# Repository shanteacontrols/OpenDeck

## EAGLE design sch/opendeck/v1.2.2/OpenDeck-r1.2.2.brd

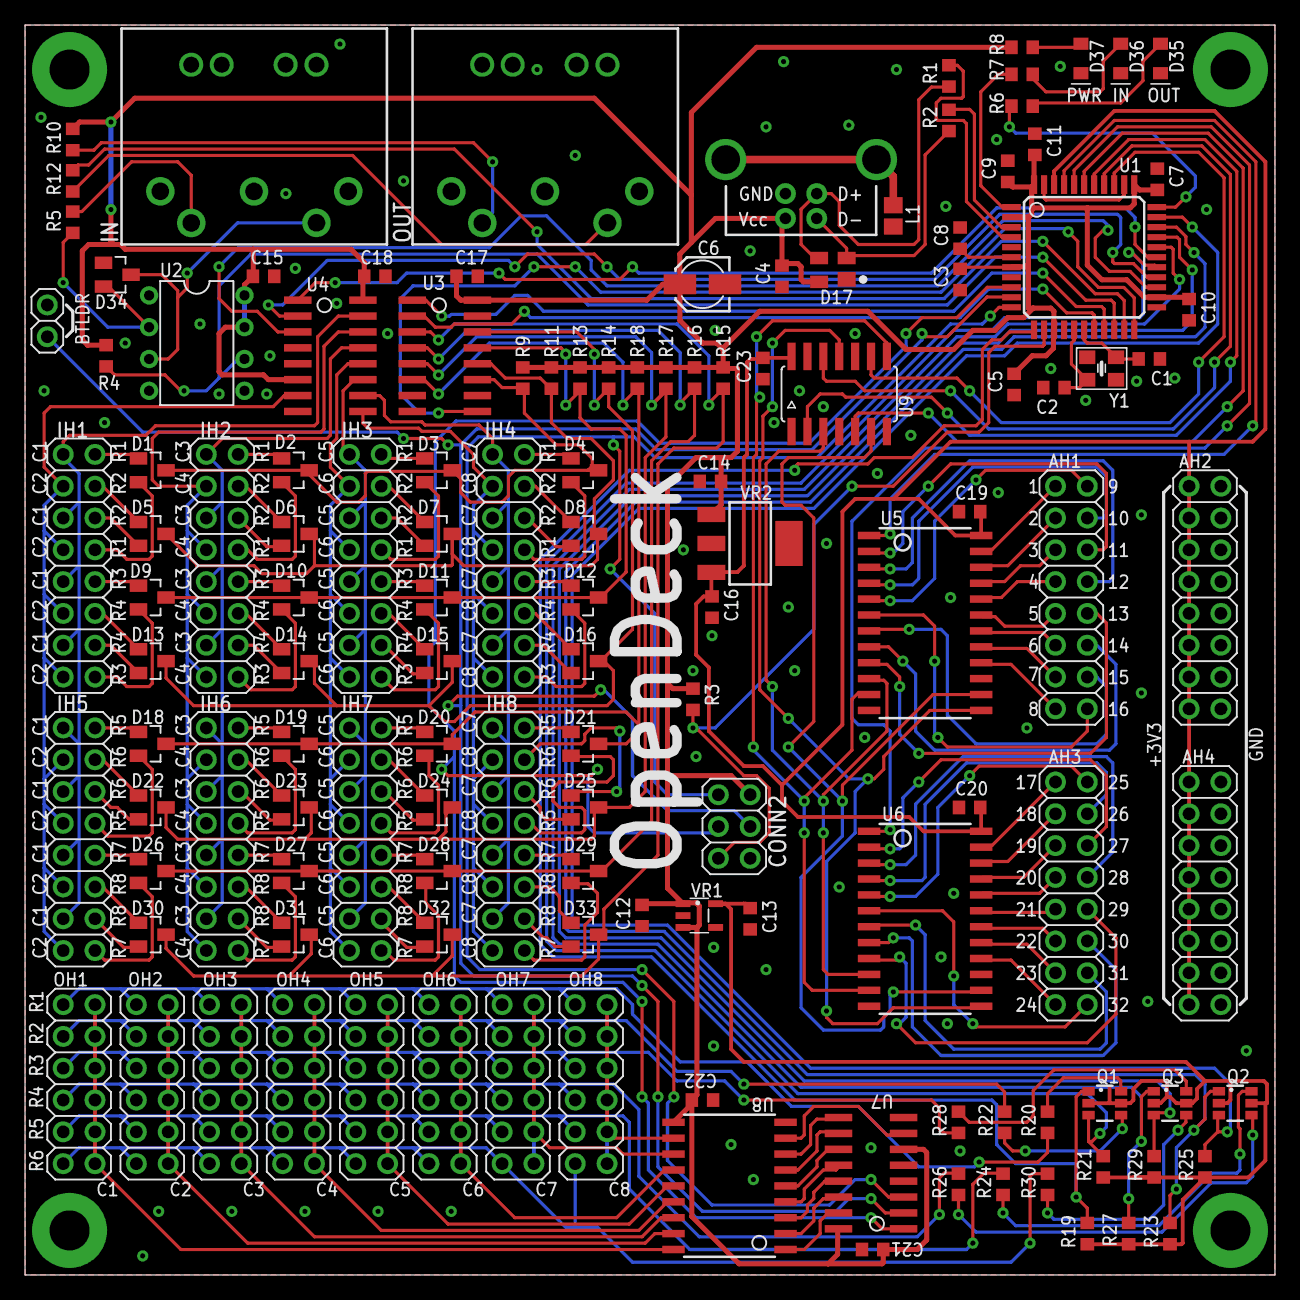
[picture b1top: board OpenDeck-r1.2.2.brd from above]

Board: 2 copper layers, 99.8 x 99.8 mm, 131 parts (0 on the bottom side), 190 nets.

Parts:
AH1, AH2, AH3, AH4: PINHD-2X08-TH-2.54MM; 2X08-2.54
C1, C2: 22p; C0603
C3, C4, C5, C7, C9, C10, C11, C15, C17, C18, C19, C20, C21, C22, C23: 100n; C0603
C6: 10u; 153CLV-0405
C8: 1u; C0603
C12, C13, C14, C16: 4.7u; C0603
CONN1: USB-B-PTH
CONN2: PINHD-2X03-TH-2.54MM-V; 2X03-2.54-V
CONN3, CONN4: MIDI_CONN-STD; DIN5_SUPPORT
CONN5: PINHD-1X02-TH-2.54MM; 1X02-2.54-V
D1, D2, D3, D4, D5, D6, D7, D8, D9, D10, D11, D12, D13, D14, D15, D16, D18, D19, D20, D21, D22, D23, D24, D25, D26, D27, D28, D29, D30, D31, D32, D33, D34: BAW56; SOT23
D17: PRTR5V0U2X; SOT143
D35: Red; 0805_LED
D36: Yellow; 0805_LED
D37: Green; 0805_LED
IH1, IH2, IH3, IH4, IH5, IH6, IH7, IH8: PINHD-2X08-TH-2.54MM; 2X08-2.54
L1: FERRITE_BEAD-BLM21PG221SN1D; L0805
OH1, OH2, OH3, OH4, OH5, OH6, OH7, OH8: PINHD-2X06-TH-2.54MM; 2X06-2.54-V
Q1, Q2, Q3: FDC6312P; SSOT6
R1, R2: 22; R0603
R3, R4, R9, R11, R13, R14, R15, R16, R17, R18: 10k; R0603
R5, R10, R12: 220; R0603
R6, R7, R8: 1k; R0603
R19, R21, R23, R25, R27, R29: 4k7; R0603
R20, R22, R24, R26, R28, R30: 47; R0603
U1: ATMEGA-32U4TQFP; TQFP-44
U2: 6N137; DIL08
U3: 74HC165; SO16
U4: 74HC138-SO; SO16
U5, U6: MC14067BDWR2G-SO24W; SO24-W
U7: 74HC238-SO; SO16
U8: ULN2803A-SO; SO18
U9: 74AHC125; SOIC14
VR1: LP5907-4.5V; SOT23-5
VR2: MCP1825; SOT223
Y1: 16MHz; CRYSTAL-SMD-3.2X2.5

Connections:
+5V: C3.1, C4.2, C5.1, C6.+, C7.1, C9.1, C10.1, C11.1, C12.1, C14.1, C15.2, C17.2, C18.2, C21.1, C22.1, CONN1.VBUS, CONN2.2, D17.4, R3.1, R4.1, R8.1, R9.1, R10.2, R11.1, R13.1, R14.1, R15.1, R16.1, R17.1, R18.1, U1.2, U1.7, U1.14, U1.24, U1.34, U1.44, U2.7, U2.8, U3.16, U4.6, U4.16, U7.6, U7.16, U8.10, VR1.1, VR1.3, VR2.1
AREF: AH2.1, AH2.3, AH2.5, AH2.7, AH2.9, AH2.11, AH2.13, AH2.15, AH4.1, AH4.3, AH4.5, AH4.7, AH4.9, AH4.11, AH4.13, AH4.15, C16.1, C19.2, C20.2, C23.2, U1.42, U5.24, U6.24, U9.14, VR2.3
A_IN_1: AH1.1, U5.23
A_IN_2: AH1.3, U5.22
A_IN_3: AH1.5, U5.21
A_IN_4: AH1.7, U5.20
A_IN_5: AH1.9, U5.19
A_IN_6: AH1.11, U5.18
A_IN_7: AH1.13, U5.17
A_IN_8: AH1.15, U5.16
A_IN_9: AH1.6, U5.2
A_IN_10: AH1.8, U5.3
A_IN_11: AH1.4, U5.4
A_IN_12: AH1.2, U5.5
A_IN_13: AH1.16, U5.6
A_IN_14: AH1.14, U5.7
A_IN_15: AH1.12, U5.8
A_IN_16: AH1.10, U5.9
A_IN_17: AH3.1, U6.23
A_IN_18: AH3.3, U6.22
A_IN_19: AH3.5, U6.21
A_IN_20: AH3.7, U6.20
A_IN_21: AH3.9, U6.19
A_IN_22: AH3.11, U6.18
A_IN_23: AH3.13, U6.17
A_IN_24: AH3.15, U6.16
A_IN_25: AH3.6, U6.2
A_IN_26: AH3.8, U6.3
A_IN_27: AH3.4, U6.4
A_IN_28: AH3.2, U6.5
A_IN_29: AH3.16, U6.6
A_IN_30: AH3.14, U6.7
A_IN_31: AH3.12, U6.8
A_IN_32: AH3.10, U6.9
BC_1: IH1.1, IH1.5, IH1.9, IH1.13, IH5.1, IH5.5, IH5.9, IH5.13, U4.15
BC_2: IH1.3, IH1.7, IH1.11, IH1.15, IH5.3, IH5.7, IH5.11, IH5.15, U4.7
BC_3: IH2.1, IH2.5, IH2.9, IH2.13, IH6.1, IH6.5, IH6.9, IH6.13, U4.13
BC_4: IH2.3, IH2.7, IH2.11, IH2.15, IH6.3, IH6.7, IH6.11, IH6.15, U4.14
BC_5: IH3.1, IH3.5, IH3.9, IH3.13, IH7.1, IH7.5, IH7.9, IH7.13, U4.11
BC_6: IH3.3, IH3.7, IH3.11, IH3.15, IH7.3, IH7.7, IH7.11, IH7.15, U4.12
BC_7: IH4.1, IH4.5, IH4.9, IH4.13, IH8.1, IH8.5, IH8.9, IH8.13, U4.10
BC_8: IH4.3, IH4.7, IH4.11, IH4.15, IH8.3, IH8.7, IH8.11, IH8.15, U4.9
BR_1: D1.3, D2.3, D3.3, D4.3, R9.2, U3.11
BR_2: D5.3, D6.3, D7.3, D8.3, R11.2, U3.12
BR_3: D9.3, D10.3, D11.3, D12.3, R13.2, U3.13
BR_4: D13.3, D14.3, D15.3, D16.3, R14.2, U3.14
BR_5: D30.3, D31.3, D32.3, D33.3, R15.2, U3.3
BR_6: D26.3, D27.3, D28.3, D29.3, R16.2, U3.4
BR_7: D22.3, D23.3, D24.3, D25.3, R17.2, U3.5
BR_8: D18.3, D19.3, D20.3, D21.3, R18.2, U3.6
D+: R1.2, U1.4
D+X: CONN1.D+, D17.3, R1.1
D-: R2.1, U1.3
D-X: CONN1.D-, D17.2, R2.2
DEC_BM_A0: U1.28, U4.1
DEC_BM_A1: U1.26, U4.2
DEC_BM_A2: U1.25, U4.3
DEC_LM_A0/SCK: CONN2.3, U1.9, U7.1
DEC_LM_A1/MOSI: CONN2.4, CONN5.1, U1.10, U7.2
DEC_LM_A2/MISO: CONN2.1, U1.11, U7.3
DEC_LM_Y0: U7.15, U8.1
DEC_LM_Y1: U7.14, U8.2
DEC_LM_Y2: U7.13, U8.3
DEC_LM_Y3: U7.12, U8.4
DEC_LM_Y4: U7.11, U8.5
DEC_LM_Y5: U7.10, U8.6
DEC_LM_Y6: U7.9, U8.7
DEC_LM_Y7: U7.7, U8.8
GND: AH2.2, AH2.4, AH2.6, AH2.8, AH2.10, AH2.12, AH2.14, AH2.16, AH4.2, AH4.4, AH4.6, AH4.8, AH4.10, AH4.12, AH4.14, AH4.16, C1.2, C2.2, C3.2, C4.1, C5.2, C6.-, C7.2, C8.2, C9.2, C10.2, C11.2, C12.2, C13.2, C14.2, C15.1, C16.2, C17.1, C18.1, C19.1, C20.1, C21.2, C22.2, C23.1, CONN1.GND, CONN2.6, CONN4.2, CONN5.2, D17.1, D35.C, D36.C, D37.C, L1.1, U1.5, U1.15, U1.23, U1.35, U1.43, U2.5, U3.8, U3.15, U4.4, U4.5, U4.8, U5.12, U5.15, U6.12, U6.15, U7.4, U7.5, U7.8, U8.9, U9.1, U9.4, U9.7, U9.10, U9.13, VR1.2, VR2.2, VR2.4
IH1_2: D1.1, IH1.2
IH1_4: D5.1, IH1.4
IH1_6: D5.2, IH1.6
IH1_8: D1.2, IH1.8
IH1_10: D9.1, IH1.10
IH1_12: D13.1, IH1.12
IH1_14: D13.2, IH1.14
IH1_16: D9.2, IH1.16
IH2_2: D2.1, IH2.2
IH2_4: D6.1, IH2.4
IH2_6: D6.2, IH2.6
IH2_8: D2.2, IH2.8
IH2_10: D10.1, IH2.10
IH2_12: D14.1, IH2.12
IH2_14: D14.2, IH2.14
IH2_16: D10.2, IH2.16
IH3_2: D3.1, IH3.2
IH3_4: D7.1, IH3.4
IH3_6: D7.2, IH3.6
IH3_8: D3.2, IH3.8
IH3_10: D11.1, IH3.10
IH3_12: D15.1, IH3.12
IH3_14: D15.2, IH3.14
IH3_16: D11.2, IH3.16
IH4_2: D4.1, IH4.2
IH4_4: D8.1, IH4.4
IH4_6: D8.2, IH4.6
IH4_8: D4.2, IH4.8
IH4_10: D12.1, IH4.10
IH4_12: D16.1, IH4.12
IH4_14: D16.2, IH4.14
IH4_16: D12.2, IH4.16
IH5_2: D18.1, IH5.2
IH5_4: D22.1, IH5.4
IH5_6: D22.2, IH5.6
IH5_8: D18.2, IH5.8
IH5_10: D26.1, IH5.10
IH5_12: D30.1, IH5.12
IH5_14: D30.2, IH5.14
IH5_16: D26.2, IH5.16
IH6_2: D19.1, IH6.2
IH6_4: D23.1, IH6.4
IH6_6: D23.2, IH6.6
IH6_8: D19.2, IH6.8
IH6_10: D27.1, IH6.10
IH6_12: D31.1, IH6.12
IH6_14: D31.2, IH6.14
IH6_16: D27.2, IH6.16
IH7_2: D20.1, IH7.2
IH7_4: D24.1, IH7.4
IH7_6: D24.2, IH7.6
IH7_8: D20.2, IH7.8
IH7_10: D28.1, IH7.10
IH7_12: D32.1, IH7.12
IH7_14: D32.2, IH7.14
IH7_16: D28.2, IH7.16
IH8_2: D21.1, IH8.2
IH8_4: D25.1, IH8.4
IH8_6: D25.2, IH8.6
IH8_8: D21.2, IH8.8
IH8_10: D29.1, IH8.10
IH8_12: D33.1, IH8.12
IH8_14: D33.2, IH8.14
IH8_16: D29.2, IH8.16
LC_1: OH1.2, OH1.4, OH1.6, OH1.8, OH1.10, OH1.12, U8.18
LC_2: OH2.2, OH2.4, OH2.6, OH2.8, OH2.10, OH2.12, U8.17
LC_3: OH3.2, OH3.4, OH3.6, OH3.8, OH3.10, OH3.12, U8.16
LC_4: OH4.2, OH4.4, OH4.6, OH4.8, OH4.10, OH4.12, U8.15
LC_5: OH5.2, OH5.4, OH5.6, OH5.8, OH5.10, OH5.12, U8.14
LC_6: OH6.2, OH6.4, OH6.6, OH6.8, OH6.10, OH6.12, U8.13
LC_7: OH7.2, OH7.4, OH7.6, OH7.8, OH7.10, OH7.12, U8.12
LC_8: OH8.2, OH8.4, OH8.6, OH8.8, OH8.10, OH8.12, U8.11
LEDS_VCC: C13.1, Q1.2, Q1.5, Q2.2, Q2.5, Q3.2, Q3.5, R19.1, R21.1, R23.1, R25.1, R27.1, R29.1, VR1.5
LR_1_MI: Q1.1, R19.2, U1.12
LR_1_MO: OH1.1, OH2.1, OH3.1, OH4.1, OH5.1, OH6.1, OH7.1, OH8.1, R20.1
LR_1_MO_R: Q1.6, R20.2
LR_2_MI: Q1.3, R21.2, U1.27
LR_2_MO: OH1.3, OH2.3, OH3.3, OH4.3, OH5.3, OH6.3, OH7.3, OH8.3, R22.2
LR_2_MO_R: Q1.4, R22.1
LR_3_MI: Q3.1, R27.2, U1.29
LR_3_MO: OH1.5, OH2.5, OH3.5, OH4.5, OH5.5, OH6.5, OH7.5, OH8.5, R28.1
LR_3_MO_R: Q3.6, R28.2
LR_4_MI: Q2.3, R25.2, U1.32
LR_4_MO: OH1.7, OH2.7, OH3.7, OH4.7, OH5.7, OH6.7, OH7.7, OH8.7, R26.1
LR_4_MO_R: Q2.4, R26.2
LR_5_MI: Q2.1, R23.2, U1.31
LR_5_MO: OH1.9, OH2.9, OH3.9, OH4.9, OH5.9, OH6.9, OH7.9, OH8.9, R24.1
LR_5_MO_R: Q2.6, R24.2
LR_6_MI: Q3.3, R29.2, U1.30
LR_6_MO: OH1.11, OH2.11, OH3.11, OH4.11, OH5.11, OH6.11, OH7.11, OH8.11, R30.1
LR_6_MO_R: Q3.4, R30.2
MIDI_IN: R4.2, U1.20, U2.6
MIDI_IN_4: CONN3.4, R5.1
MIDI_IN_5: CONN3.5, D34.3, U2.3
MIDI_IN_DIODE_OUT: D34.2, R5.2, U2.2
MIDI_IN_LED: R7.2, U1.1
MIDI_IN_LED_R: D36.A, R7.1
MIDI_OUT: R12.2, U1.21
MIDI_OUT_4: CONN4.4, R10.1
MIDI_OUT_5: CONN4.5, R12.1
MIDI_OUT_LED: R6.2, U1.33
MIDI_OUT_LED_R: D35.A, R6.1
MUX_COMMON_1: U1.41, U5.1
MUX_COMMON_2: U1.40, U6.1
MUX_S0_3V3: U5.10, U6.10, U9.3
MUX_S0_5V: U1.38, U9.2
MUX_S1_3V3: U5.11, U6.11, U9.8
MUX_S1_5V: U1.36, U9.9
MUX_S2_3V3: U5.14, U6.14, U9.6
MUX_S2_5V: U1.39, U9.5
MUX_S3_3V3: U5.13, U6.13, U9.11
MUX_S3_5V: U1.37, U9.12
PWR_LED_R: D37.A, R8.2
RESET: CONN2.5, R3.2, U1.13
SR_CLOCK: U1.18, U3.2
SR_OUT: U1.22, U3.9
SR_PARALLEL_LOAD: U1.19, U3.1
UCAP: C8.1, U1.6
USB_SHIELD: CONN1.S1, CONN1.S2, L1.2
XTAL1: C1.1, U1.17, Y1.3
XTAL2: C2.1, U1.16, Y1.1

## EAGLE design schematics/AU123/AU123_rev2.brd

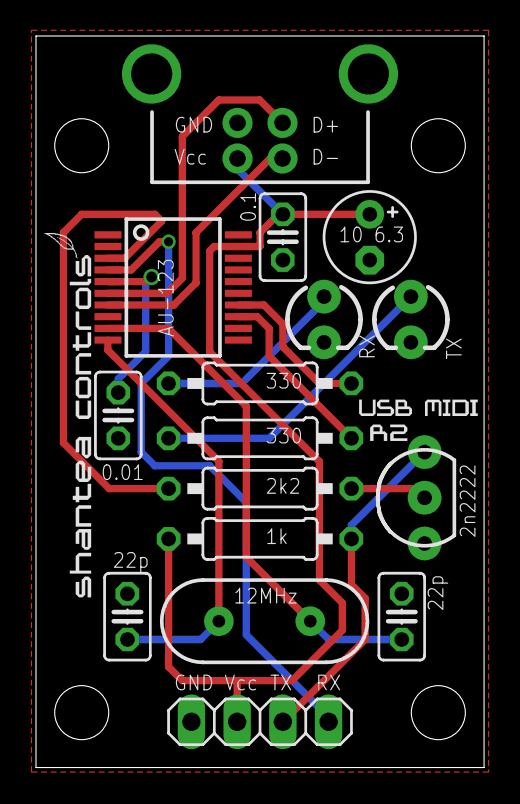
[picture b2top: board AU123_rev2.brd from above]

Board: 2 copper layers, 24.9 x 40.6 mm, 16 parts (0 on the bottom side), 15 nets.

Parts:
E$1: 1X04
E$2, E$3, E$4, E$10: C025-025X050
E$5, E$6, E$7, E$14: 0207/10
E$8, E$9: LED3MM
E$11: USB-B-PTH
E$13: E2,5-5
E$16: TO-92-AMMO
E$26: SSOP20
E$56: HC49US

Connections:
D+: E$11.D+, E$26.6
D-: E$11.D-, E$26.7
GND: E$1.1, E$2.1, E$3.2, E$4.2, E$8.K, E$9.K, E$10.2, E$11.GND, E$11.S1, E$11.S2, E$13.-, E$16.1, E$26.1, E$26.8, E$26.17
MIDI_OUT: E$5.2, E$26.3
MID_IN: E$1.4, E$26.4
RX_LED: E$6.1, E$9.A
S$4: E$6.2, E$26.14
S$7: E$5.1, E$16.2
S$8: E$1.3, E$14.1, E$16.3
TX: E$7.2, E$26.13
TX_LED: E$7.1, E$8.A
V3: E$10.1, E$26.5
VCC: E$1.2, E$2.2, E$11.VBUS, E$13.+, E$14.2, E$26.19
XI: E$4.1, E$26.9, E$56.2
XO: E$3.1, E$26.10, E$56.1

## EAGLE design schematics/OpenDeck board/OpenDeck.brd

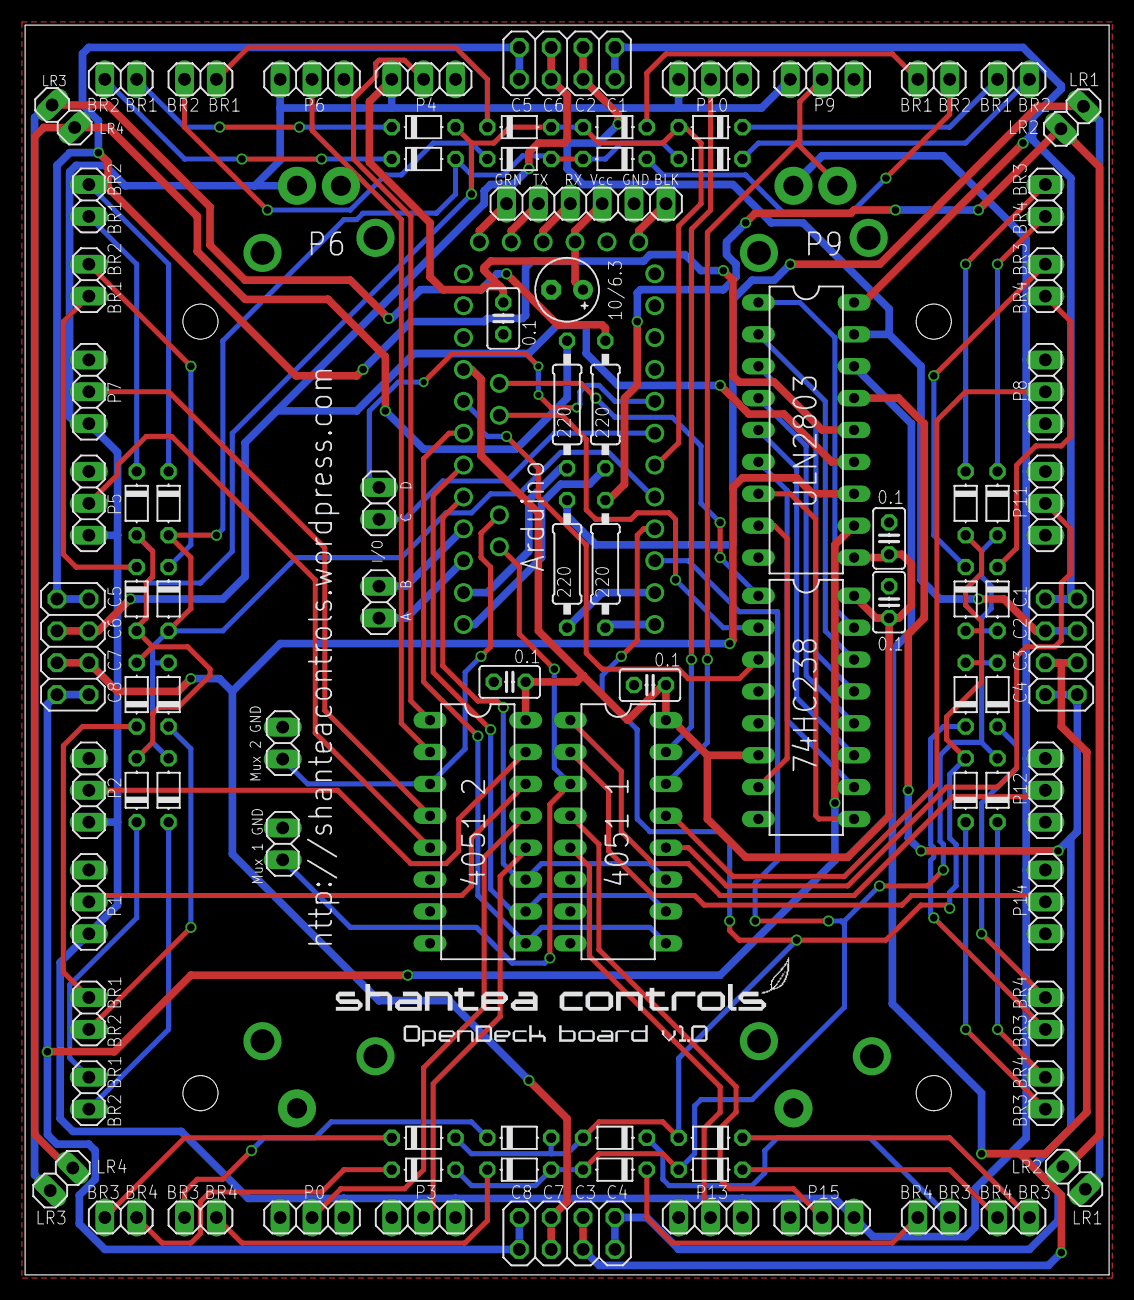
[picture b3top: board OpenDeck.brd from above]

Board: 2 copper layers, 86.4 x 99.6 mm, 92 parts (1 on the bottom side), 95 nets.

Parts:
E$1: ARDUINO_PRO_MINI
E$2, E$3, E$7, E$11, E$14, E$18, E$22, E$35, E$41, E$42, E$43, E$46, E$47, E$62, E$64, E$73, E$74, E$82, E$87, E$88, E$94, E$95, E$96, E$97: 1X02
E$4, E$32, E$33, E$81: 0207/10
E$5: E2,5-5
E$6, E$9, E$20, E$63: 2X04
E$8, E$48, E$51, E$52, E$53, E$54, E$59, E$60, E$61, E$75, E$76, E$77, E$78, E$98, E$100, E$101: 1X03
E$10, E$12, E$16, E$17, E$19, E$21, E$23, E$24, E$25, E$26, E$27, E$28, E$29, E$30, E$31, E$34, E$36, E$37, E$38, E$39, E$40, E$44, E$45, E$65, E$66, E$67, E$68, E$69, E$70, E$71, E$72, E$92: D-5
E$13, E$49, E$84: DIL16
E$15, E$50, E$85, E$86, E$89: C025-025X050
E$80: DIL18
E$83: 1X06

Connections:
B_ROW_1: E$1.7, E$12.A, E$17.A, E$21.A, E$24.A, E$66.A, E$68.A, E$70.A, E$72.A
B_ROW_2: E$1.8, E$10.A, E$16.A, E$19.A, E$23.A, E$65.A, E$67.A, E$69.A, E$71.A
B_ROW_3: E$1.9, E$27.A, E$28.A, E$30.A, E$34.A, E$38.A, E$39.A, E$44.A, E$92.A
B_ROW_4: E$1.10, E$25.A, E$26.A, E$29.A, E$31.A, E$36.A, E$37.A, E$40.A, E$45.A
COLUMN_1: E$9.7, E$9.8, E$20.7, E$20.8, E$80.18
COLUMN_2: E$9.5, E$9.6, E$20.5, E$20.6, E$80.17
COLUMN_3: E$6.5, E$6.6, E$9.3, E$9.4, E$80.16
COLUMN_4: E$6.7, E$6.8, E$9.1, E$9.2, E$80.15
COLUMN_5: E$20.1, E$20.2, E$63.7, E$63.8, E$80.14
COLUMN_6: E$20.3, E$20.4, E$63.5, E$63.6, E$80.13
COLUMN_7: E$6.3, E$6.4, E$63.3, E$63.4, E$80.12
COLUMN_8: E$6.1, E$6.2, E$63.1, E$63.2, E$80.11
DEC_0: E$1.A5, E$84.1
DEC_1: E$1.A4, E$84.2
DEC_2: E$1.20, E$84.3
DEC_OUT_0: E$80.1, E$84.15
DEC_OUT_1: E$80.2, E$84.14
DEC_OUT_2: E$80.3, E$84.13
DEC_OUT_3: E$80.4, E$84.12
DEC_OUT_4: E$80.5, E$84.11
DEC_OUT_5: E$80.6, E$84.10
DEC_OUT_6: E$80.7, E$84.9
DEC_OUT_7: E$80.8, E$84.7
GND: E$1.4, E$1.23, E$1.GND, E$5.-, E$8.3, E$13.6, E$13.7, E$13.8, E$15.2, E$48.1, E$49.6, E$49.7, E$49.8, E$50.2, E$51.1, E$52.1, E$53.1, E$54.1, E$59.1, E$60.1, E$61.1, E$75.1, E$76.1, E$77.1, E$78.1, E$80.9, E$83.5, E$84.4, E$84.5, E$84.8, E$85.1, E$86.1, E$87.2, E$88.2, E$89.2, E$98.3, E$100.3, E$101.3
LED_ROW_1: E$18.1, E$33.2, E$82.1
LED_ROW_2: E$18.2, E$32.2, E$82.2
LED_ROW_3: E$4.2, E$22.2, E$41.2
LED_ROW_4: E$22.1, E$41.1, E$81.2
MUX_1_OUT: E$1.A7, E$49.3, E$88.1
MUX_2_OUT: E$1.A6, E$13.3, E$87.1
P0A: E$48.2, E$49.13
P1: E$13.13, E$101.2
P1A: E$49.14, E$54.2
P2: E$13.14, E$75.2
P2A: E$49.15, E$53.2
P3: E$13.15, E$76.2
P3A: E$49.12, E$59.2
P4: E$13.12, E$100.2
P4A: E$49.1, E$77.2
P5: E$8.2, E$13.1
P5A: E$49.5, E$52.2
P6: E$13.5, E$60.2
P6A: E$49.2, E$78.2
P7: E$13.2, E$98.2
P7A: E$49.4, E$51.2
P8: E$13.4, E$61.2
S0: E$1.17, E$13.11, E$49.11
S1: E$1.18, E$13.10, E$49.10
S2: E$1.19, E$13.9, E$49.9
S$1: E$1.15, E$43.1
S$2: E$1.16, E$43.2
S$3: E$1.5, E$42.2
S$4: E$1.6, E$42.1
S$6: E$39.C, E$95.2
S$7: E$25.C, E$96.2
S$10: E$38.C, E$94.2
S$11: E$1.11, E$33.1
S$12: E$26.C, E$97.2
S$14: E$1.12, E$32.1
S$16: E$1.13, E$4.1
S$19: E$1.14, E$81.1
S$22: E$1.GRN, E$83.1
S$23: E$1.TXO, E$83.2
S$24: E$1.RXI, E$83.3
S$28: E$1.BLK, E$83.6
S$52: E$2.1, E$31.C
S$53: E$2.2, E$30.C
S$54: E$11.1, E$29.C
S$55: E$11.2, E$28.C
S$56: E$36.C, E$47.2
S$57: E$34.C, E$47.1
S$58: E$45.C, E$46.2
S$59: E$44.C, E$46.1
S$60: E$12.C, E$35.1
S$61: E$10.C, E$35.2
S$62: E$3.2, E$24.C
S$63: E$3.1, E$23.C
S$64: E$14.2, E$21.C
S$65: E$14.1, E$19.C
S$66: E$7.2, E$16.C
S$67: E$7.1, E$17.C
S$69: E$92.C, E$96.1
S$70: E$40.C, E$95.1
S$73: E$27.C, E$97.1
S$74: E$37.C, E$94.1
S$76: E$71.C, E$73.1
S$77: E$72.C, E$73.2
S$78: E$64.2, E$65.C
S$79: E$64.1, E$66.C
S$80: E$70.C, E$74.2
S$81: E$69.C, E$74.1
S$82: E$62.1, E$68.C
S$83: E$62.2, E$67.C
VCCA: E$1.VCC, E$5.+, E$8.1, E$48.3, E$51.3, E$52.3, E$53.3, E$54.3, E$59.3, E$60.3, E$61.3, E$75.3, E$76.3, E$77.3, E$78.3, E$83.4, E$89.1, E$98.1, E$100.1, E$101.1
VCCD: E$1.21, E$13.16, E$15.1, E$49.16, E$50.1, E$80.10, E$84.6, E$84.16, E$85.2, E$86.2

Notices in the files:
parts and their libraries:
SparkFun-RF: Licensing: CC v3.0 Share-Alike You are welcome to use this library for commercial purposes.
SparkFun-DiscreteSemi: Licensing: Creative Commons ShareAlike 4.0 International - https://creativecommons.org/licenses/by-sa/4.0
